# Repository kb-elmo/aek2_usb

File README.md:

# AEK II USB

[![CC BY-NC-SA 4.0][cc-by-nc-sa-shield]][cc-by-nc-sa]

## This project is completed and will not get updated anymore.

#### QMK compatible drop-in replacement PCB for the Apple Extended Keyboard II
The PCB is built entirely with THT parts to keep a somewhat "vintage" look to it and it uses the fullsize 40-pin DIP package ATmega32A.
The controller is placed in the exact same location as the one on the original PCB.

### Partslist
Most of the parts in this list are just examples and they can be replaced with any component with the same specs.  
They don't have to be from any specific manufacturer or brand to work on this board.

The USB breakout PCB/Daughterboard is NOT included in this repo. You will have to find one yourself.  
Pretty much any kind of breakout board that has usable VCC, GND, D+ and D- pins should work for this.  
Example: https://www.adafruit.com/product/1764

|Count|Part|Designator|Octopart URL|
|-|-|-|-|
|1|ATmega32A 40 pin DIP (32L works too)|U1|[Atmega32a-pu](https://octopart.com/atmega32a-pu-microchip-77760288)|
|1|40 pin DIP socket (optional but highly recommended)|U1|[TE Connectivity 1-2199299-5](https://octopart.com/1-2199299-5-te+connectivity-34963610)|
|1|2x3 pin header 2.54mm (for ISP flashing)|AVR1|[Würth 61200621721](https://octopart.com/61200621721-würth+elektronik-32855457)| 
|1|JST PH 2mm 4pin connector + cable|J1, J2|[JST S4B-PH-K-S](https://octopart.com/s4b-ph-k-s+%28lf%29%28sn%29-jst-5373077)|
|1|USB breakout PCB||[Adafruit 1833](https://octopart.com/1833-adafruit+industries-53099556)|
|1|500 mA polyfuse|F1|[Bourns MF-R050](https://octopart.com/mf-r050-bourns-19418)|
|2|6mm momentary push buttons|RESET1, BOOT1|[TE Connectivity 1825910-6](https://octopart.com/1825910-6-te+connectivity-42270338)|
|1|16 MHz quarz crystal|XTAL1|[Raltron AS-16.000-18](https://octopart.com/as-16.000-18-raltron+electronics-973373)|
|1|4.7 uF electrolytic capacitor|C1|[Panasonic ECA-1HM4R7I](https://octopart.com/eca-1hm4r7i-panasonic-39478610)|
|2|100 nF ceramic disk capacitor|C2, C3|[Kemet C315C104M5U5TA](https://octopart.com/c315c104m5u5ta-kemet-83288)|
|2|22 pF ceramic disk capacitor|C4, C5|[Kemet C317C220J1G5TA](https://octopart.com/c317c220j1g5ta-kemet-1747641)|
|1|10 kΩ resistor|R4|[Multicomp MF25 10k](https://octopart.com/mf25+10k-multicomp-2697429)|
|2|68 Ω resistor|R2, R3|[Multicomp MF25 68R](https://octopart.com/mf25+68r-multicomp-5364489)|
|4|1.5 kΩ resistor|R1, R5, R6, R7|[Multicomp MF25 1k5](https://octopart.com/mf25+1k5-multicomp-5372506)|
|3|5mm LED (for the lock indicators)|LED1, LED2, LED3|[Vishay TLHG5400](https://octopart.com/tlhg5400-vishay-39403037)|
|2|3.6 V zener diode (DO-35 BZX55C3V6)|D1, D2|[ON Semiconductor BZX85C3V6](https://octopart.com/bzx85c3v6-on+semiconductor-84409073)|
|105|universal switching diode (DO-35 1N4148)|D3-D107|[ON Semiconductor 1N4148](https://octopart.com/1n4148-on+semiconductor-6807167)|

#### Some pictures of the first finished PCB

---
This work is licensed under a
[Creative Commons Attribution-NonCommercial-ShareAlike 4.0 International License][cc-by-nc-sa].

[![CC BY-NC-SA 4.0][cc-by-nc-sa-image]][cc-by-nc-sa]

[cc-by-nc-sa]: http://creativecommons.org/licenses/by-nc-sa/4.0/
[cc-by-nc-sa-image]: https://licensebuttons.net/l/by-nc-sa/4.0/88x31.png
[cc-by-nc-sa-shield]: https://img.shields.io/badge/License-CC%20BY--NC--SA%204.0-lightgrey.svg

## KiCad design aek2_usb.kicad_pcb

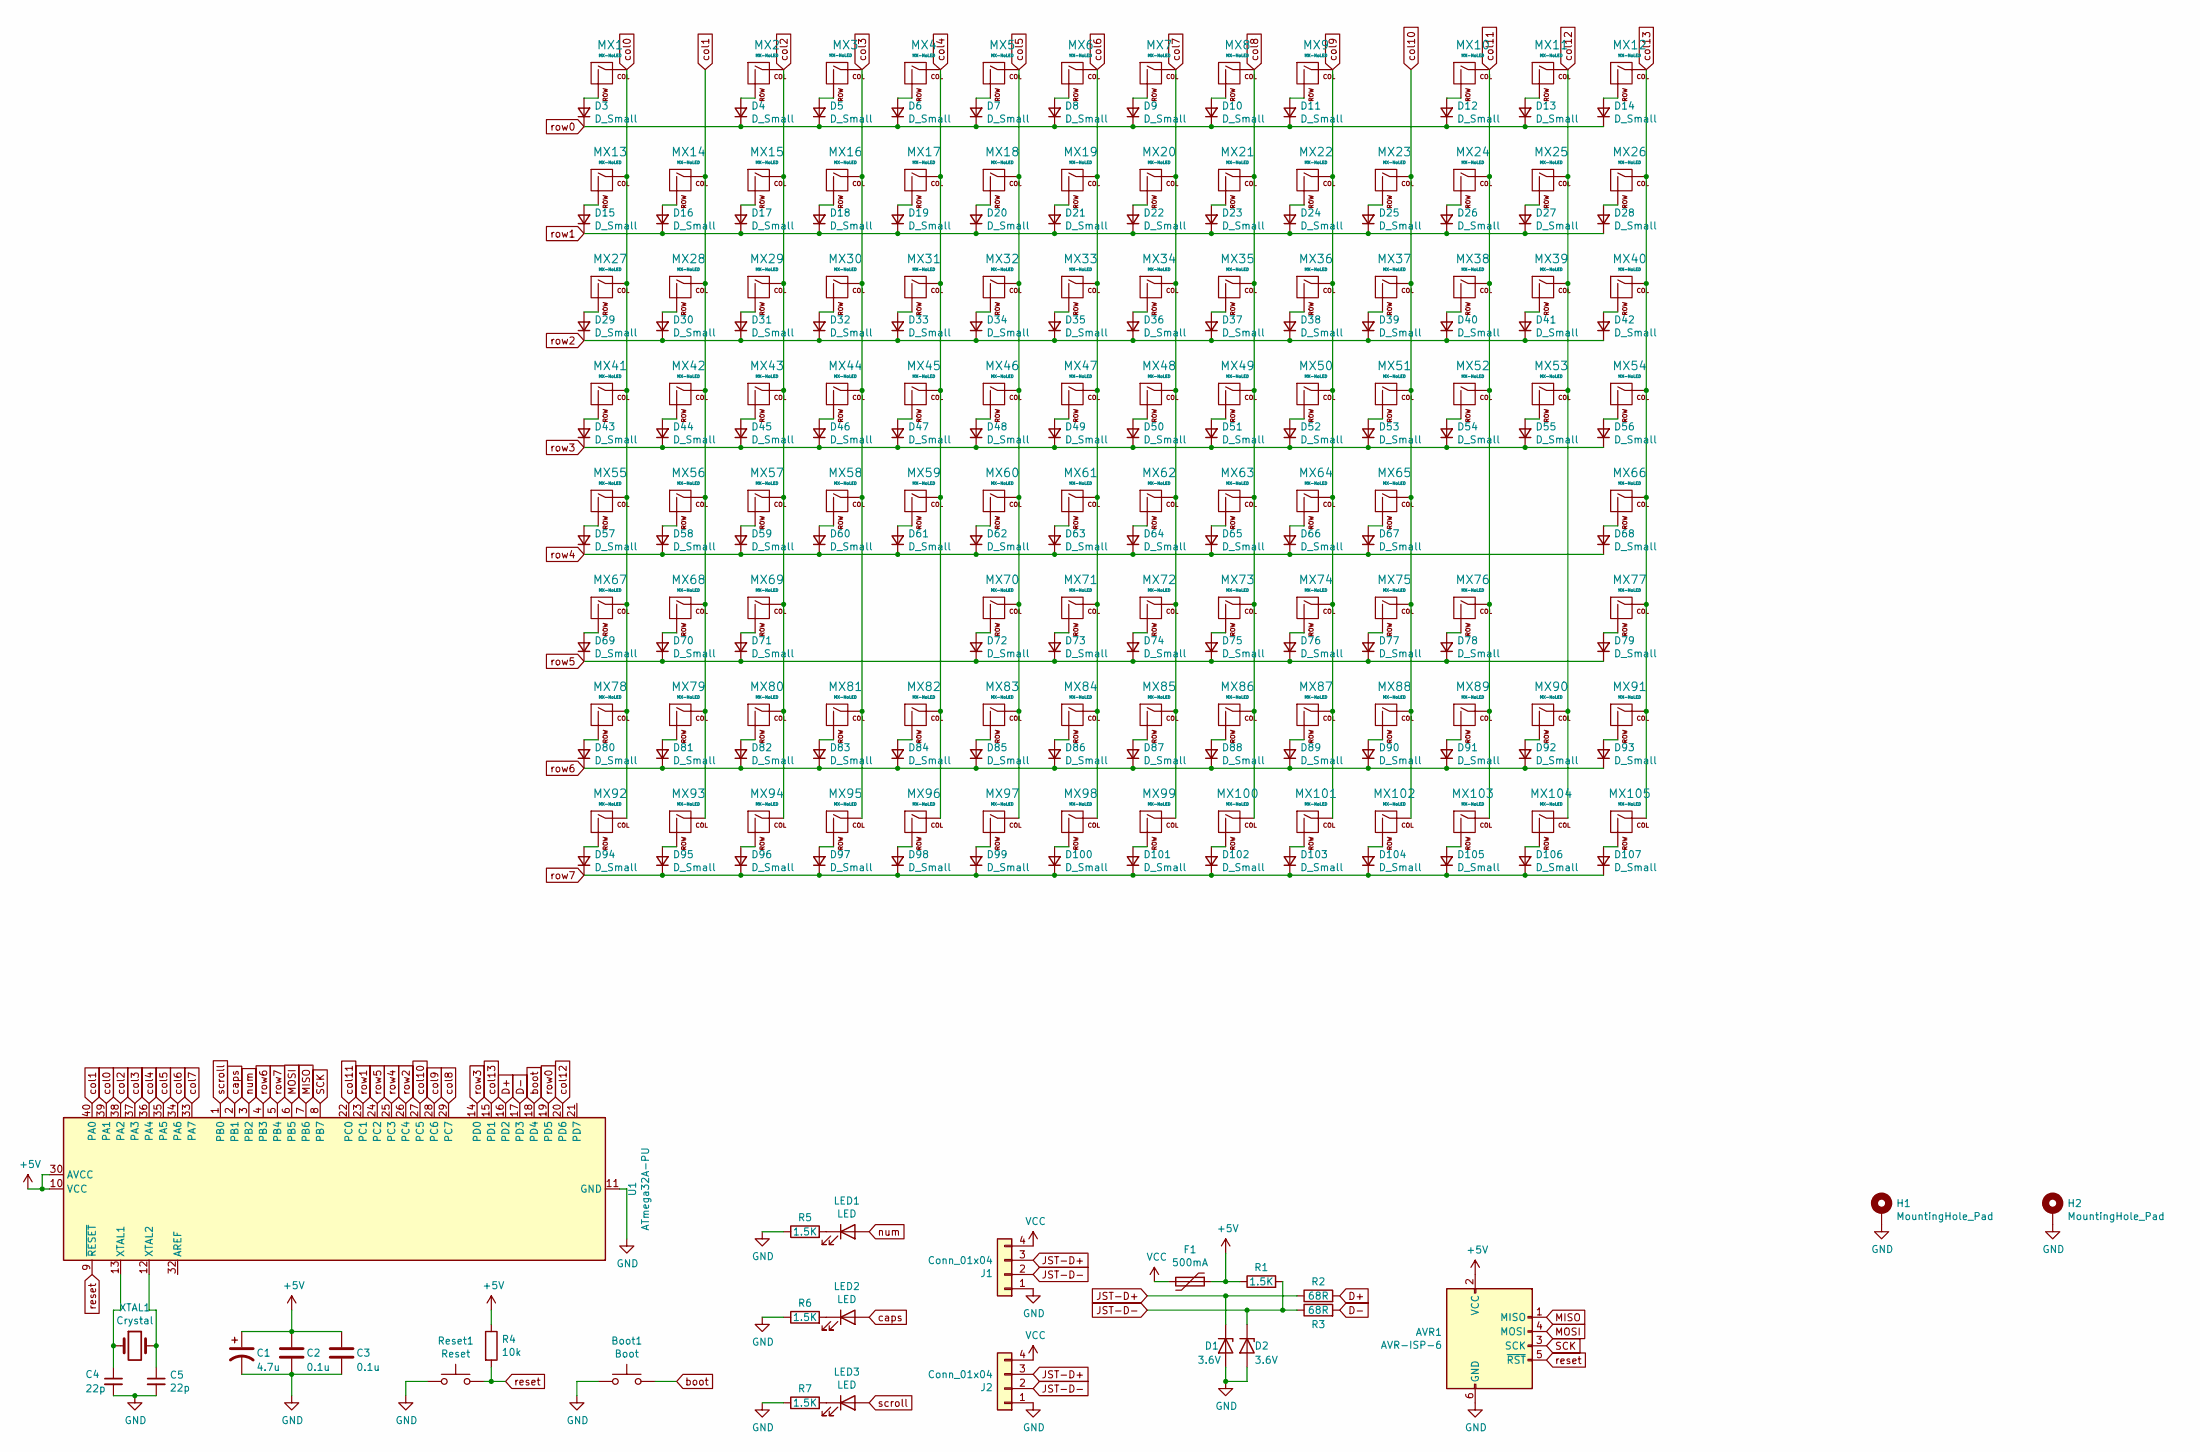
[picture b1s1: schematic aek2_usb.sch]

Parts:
AVR1: AVR-ISP-6; PinHeader_2x03_P2.54mm_Horizontal
Boot1: Boot; SW_PUSH_6mm
C1: 4.7u; CP_Radial_D5.0mm_P2.50mm
C2, C3: 0.1u; C_Disc_D3.0mm_W2.0mm_P2.50mm
C4, C5: 22p; C_Disc_D6.0mm_W2.5mm_P5.00mm
D1, D2: 3.6V; D_DO-35_SOD27_P7.62mm_Horizontal
D3, D4, D5, D6, D7, D8, D9, D10, D11, D12, D13, D14, D15, D16, D17, D18, D19, D20, D21, D22, D23, D24, D25, D26, D27, D28, D29, D30, D31, D32, D33, D34, D35, D36, D37, D38, D39, D40, D41, D42, D43, D44, D45, D46, D47, D48, D49, D50, D51, D52, D53, D54, D55, D56, D57, D58, D59, D60, D61, D62, D63, D64, D65, D66, D67, D68, D69, D70, D71, D72, D73, D74, D75, D76, D77, D78, D79, D80, D81, D82, D83, D84, D85, D86, D87, D88, D89, D90, D91, D92, D93, D94, D95, D96, D97, D98, D99, D100, D101, D102, D103, D104, D105, D106, D107: D_Small; D_DO-35_SOD27_P7.62mm_Horizontal
F1: 500mA; Fuse_Littelfuse_395Series
H1, H2: MountingHole_Pad; screw-hole
J1, J2: Conn_01x04; JST_PH_S4B-PH-K_1x04_P2.00mm_Horizontal
LED1, LED2, LED3: LED; LED_D5.0mm
MX1, MX2, MX3, MX4, MX5, MX6, MX7, MX8, MX9, MX10, MX11, MX12, MX13, MX14, MX15, MX16, MX17, MX18, MX19, MX20, MX21, MX22, MX23, MX24, MX25, MX28, MX29, MX30, MX31, MX32, MX33, MX34, MX35, MX36, MX37, MX38, MX39, MX42, MX43, MX44, MX45, MX46, MX47, MX48, MX49, MX50, MX51, MX52, MX53, MX56, MX57, MX58, MX59, MX60, MX61, MX62, MX63, MX64, MX65, MX70, MX71, MX72, MX73, MX74, MX78, MX79, MX80, MX81, MX82, MX83, MX84, MX85, MX86, MX87, MX88, MX89, MX90, MX91, MX92, MX93, MX94, MX95, MX96, MX97, MX98, MX99, MX101, MX103, MX104, MX105: MX-NoLED; ALPS-1U
MX26, MX100, MX102: MX-NoLED; ALPS-2U
MX27, MX40, MX67, MX69, MX75, MX77: MX-NoLED; ALPS-1.5U
MX41: MX-NoLED; ALPS-1.75U
MX54, MX55: MX-NoLED; ALPS-2.25U
MX66: MX-NoLED; ALPS-2.75U
MX68, MX76: MX-NoLED; ALPS-1.25U
R1, R5, R6, R7: 1.5K; R_Axial_DIN0207_L6.3mm_D2.5mm_P10.16mm_Horizontal
R2, R3: 68R; R_Axial_DIN0207_L6.3mm_D2.5mm_P10.16mm_Horizontal
R4: 10k; R_Axial_DIN0207_L6.3mm_D2.5mm_P10.16mm_Horizontal
Reset1: Reset; SW_PUSH_6mm
U1: ATmega32A-PU; DIP-40_W15.24mm_Socket
XTAL1: Crystal; Crystal_HC49-4H_Vertical

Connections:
+5V: AVR1.2 (VCC), C1.1, C2.1, C3.1, F1.1, R1.1, R4.1, U1.10 (VCC), U1.30 (AVCC)
D+: R2.2, U1.16 (PD2)
D-: R3.2, U1.17 (PD3)
GND: AVR1.6 (GND), Boot1.1, C1.2, C2.2, C3.2, C4.2, C5.2, D1.2 (A), D2.2 (A), H1.1, H2.1, J1.1, J2.1, R5.1, R6.1, R7.1, Reset1.1, U1.11 (GND), U1.31 (GND)
JST-D+: D1.1 (K), J1.3, J2.3, R2.1
JST-D-: D2.1 (K), J1.2, J2.2, R1.2, R3.1
MISO: AVR1.1 (MISO), U1.7 (PB6)
MOSI: AVR1.4 (MOSI), U1.6 (PB5)
unnamed: C4.1, U1.13 (XTAL1), XTAL1.1
unnamed: C5.1, U1.12 (XTAL2), XTAL1.2
unnamed: D3.2 (A), MX1.2 (ROW)
unnamed: D4.2 (A), MX2.2 (ROW)
unnamed: D5.2 (A), MX3.2 (ROW)
unnamed: D6.2 (A), MX4.2 (ROW)
unnamed: D7.2 (A), MX5.2 (ROW)
unnamed: D8.2 (A), MX6.2 (ROW)
unnamed: D9.2 (A), MX7.2 (ROW)
unnamed: D10.2 (A), MX8.2 (ROW)
unnamed: D11.2 (A), MX9.2 (ROW)
unnamed: D12.2 (A), MX10.2 (ROW)
unnamed: D13.2 (A), MX11.2 (ROW)
unnamed: D14.2 (A), MX12.2 (ROW)
unnamed: D15.2 (A), MX13.2 (ROW)
unnamed: D16.2 (A), MX14.2 (ROW)
unnamed: D17.2 (A), MX15.2 (ROW)
unnamed: D18.2 (A), MX16.2 (ROW)
unnamed: D19.2 (A), MX17.2 (ROW)
unnamed: D20.2 (A), MX18.2 (ROW)
unnamed: D21.2 (A), MX19.2 (ROW)
unnamed: D22.2 (A), MX20.2 (ROW)
unnamed: D23.2 (A), MX21.2 (ROW)
unnamed: D24.2 (A), MX22.2 (ROW)
unnamed: D25.2 (A), MX23.2 (ROW)
unnamed: D26.2 (A), MX24.2 (ROW)
unnamed: D27.2 (A), MX25.2 (ROW)
unnamed: D28.2 (A), MX26.2 (ROW)
unnamed: D29.2 (A), MX27.2 (ROW)
unnamed: D30.2 (A), MX28.2 (ROW)
unnamed: D31.2 (A), MX29.2 (ROW)
unnamed: D32.2 (A), MX30.2 (ROW)
unnamed: D33.2 (A), MX31.2 (ROW)
unnamed: D34.2 (A), MX32.2 (ROW)
unnamed: D35.2 (A), MX33.2 (ROW)
unnamed: D36.2 (A), MX34.2 (ROW)
unnamed: D37.2 (A), MX35.2 (ROW)
unnamed: D38.2 (A), MX36.2 (ROW)
unnamed: D39.2 (A), MX37.2 (ROW)
unnamed: D40.2 (A), MX38.2 (ROW)
unnamed: D41.2 (A), MX39.2 (ROW)
unnamed: D42.2 (A), MX40.2 (ROW)
unnamed: D43.2 (A), MX41.2 (ROW)
unnamed: D44.2 (A), MX42.2 (ROW)
unnamed: D45.2 (A), MX43.2 (ROW)
unnamed: D46.2 (A), MX44.2 (ROW)
unnamed: D47.2 (A), MX45.2 (ROW)
unnamed: D48.2 (A), MX46.2 (ROW)
unnamed: D49.2 (A), MX47.2 (ROW)
unnamed: D50.2 (A), MX48.2 (ROW)
unnamed: D51.2 (A), MX49.2 (ROW)
unnamed: D52.2 (A), MX50.2 (ROW)
unnamed: D53.2 (A), MX51.2 (ROW)
unnamed: D54.2 (A), MX52.2 (ROW)
unnamed: D55.2 (A), MX53.2 (ROW)
unnamed: D56.2 (A), MX54.2 (ROW)
unnamed: D57.2 (A), MX55.2 (ROW)
unnamed: D58.2 (A), MX56.2 (ROW)
unnamed: D59.2 (A), MX57.2 (ROW)
unnamed: D60.2 (A), MX58.2 (ROW)
unnamed: D61.2 (A), MX59.2 (ROW)
unnamed: D62.2 (A), MX60.2 (ROW)
unnamed: D63.2 (A), MX61.2 (ROW)
unnamed: D64.2 (A), MX62.2 (ROW)
unnamed: D65.2 (A), MX63.2 (ROW)
unnamed: D66.2 (A), MX64.2 (ROW)
unnamed: D67.2 (A), MX65.2 (ROW)
unnamed: D68.2 (A), MX66.2 (ROW)
unnamed: D69.2 (A), MX67.2 (ROW)
unnamed: D70.2 (A), MX68.2 (ROW)
unnamed: D71.2 (A), MX69.2 (ROW)
unnamed: D72.2 (A), MX70.2 (ROW)
unnamed: D73.2 (A), MX71.2 (ROW)
unnamed: D74.2 (A), MX72.2 (ROW)
unnamed: D75.2 (A), MX73.2 (ROW)
unnamed: D76.2 (A), MX74.2 (ROW)
unnamed: D77.2 (A), MX75.2 (ROW)
unnamed: D78.2 (A), MX76.2 (ROW)
unnamed: D79.2 (A), MX77.2 (ROW)
unnamed: D80.2 (A), MX78.2 (ROW)
unnamed: D81.2 (A), MX79.2 (ROW)
unnamed: D82.2 (A), MX80.2 (ROW)
unnamed: D83.2 (A), MX81.2 (ROW)
unnamed: D84.2 (A), MX82.2 (ROW)
unnamed: D85.2 (A), MX83.2 (ROW)
unnamed: D86.2 (A), MX84.2 (ROW)
unnamed: D87.2 (A), MX85.2 (ROW)
unnamed: D88.2 (A), MX86.2 (ROW)
unnamed: D89.2 (A), MX87.2 (ROW)
unnamed: D90.2 (A), MX88.2 (ROW)
unnamed: D91.2 (A), MX89.2 (ROW)
unnamed: D92.2 (A), MX90.2 (ROW)
unnamed: D93.2 (A), MX91.2 (ROW)
unnamed: D94.2 (A), MX92.2 (ROW)
unnamed: D95.2 (A), MX93.2 (ROW)
unnamed: D96.2 (A), MX94.2 (ROW)
unnamed: D97.2 (A), MX95.2 (ROW)
unnamed: D98.2 (A), MX96.2 (ROW)
unnamed: D99.2 (A), MX97.2 (ROW)
unnamed: D100.2 (A), MX98.2 (ROW)
unnamed: D101.2 (A), MX99.2 (ROW)
unnamed: D102.2 (A), MX100.2 (ROW)
unnamed: D103.2 (A), MX101.2 (ROW)
unnamed: D104.2 (A), MX102.2 (ROW)
unnamed: D105.2 (A), MX103.2 (ROW)
unnamed: D106.2 (A), MX104.2 (ROW)
unnamed: D107.2 (A), MX105.2 (ROW)
unnamed: LED1.1 (K), R5.2
unnamed: LED2.1 (K), R6.2
unnamed: LED3.1 (K), R7.2
SCK: AVR1.3 (SCK), U1.8 (PB7)
VCC: F1.2, J1.4, J2.4
boot: Boot1.2, U1.18 (PD4)
caps: LED2.2 (A), U1.2 (PB1)
col0: MX1.1 (COL), MX13.1 (COL), MX27.1 (COL), MX41.1 (COL), MX55.1 (COL), MX67.1 (COL), MX78.1 (COL), MX92.1 (COL), U1.39 (PA1)
col1: MX14.1 (COL), MX28.1 (COL), MX42.1 (COL), MX56.1 (COL), MX68.1 (COL), MX79.1 (COL), MX93.1 (COL), U1.40 (PA0)
col2: MX2.1 (COL), MX15.1 (COL), MX29.1 (COL), MX43.1 (COL), MX57.1 (COL), MX69.1 (COL), MX80.1 (COL), MX94.1 (COL), U1.38 (PA2)
col3: MX3.1 (COL), MX16.1 (COL), MX30.1 (COL), MX44.1 (COL), MX58.1 (COL), MX81.1 (COL), MX95.1 (COL), U1.37 (PA3)
col4: MX4.1 (COL), MX17.1 (COL), MX31.1 (COL), MX45.1 (COL), MX59.1 (COL), MX82.1 (COL), MX96.1 (COL), U1.36 (PA4)
col5: MX5.1 (COL), MX18.1 (COL), MX32.1 (COL), MX46.1 (COL), MX60.1 (COL), MX70.1 (COL), MX83.1 (COL), MX97.1 (COL), U1.35 (PA5)
col6: MX6.1 (COL), MX19.1 (COL), MX33.1 (COL), MX47.1 (COL), MX61.1 (COL), MX71.1 (COL), MX84.1 (COL), MX98.1 (COL), U1.34 (PA6)
col7: MX7.1 (COL), MX20.1 (COL), MX34.1 (COL), MX48.1 (COL), MX62.1 (COL), MX72.1 (COL), MX85.1 (COL), MX99.1 (COL), U1.33 (PA7)
col8: MX8.1 (COL), MX21.1 (COL), MX35.1 (COL), MX49.1 (COL), MX63.1 (COL), MX73.1 (COL), MX86.1 (COL), MX100.1 (COL), U1.29 (PC7)
col9: MX9.1 (COL), MX22.1 (COL), MX36.1 (COL), MX50.1 (COL), MX64.1 (COL), MX74.1 (COL), MX87.1 (COL), MX101.1 (COL), U1.28 (PC6)
col10: MX23.1 (COL), MX37.1 (COL), MX51.1 (COL), MX65.1 (COL), MX75.1 (COL), MX88.1 (COL), MX102.1 (COL), U1.27 (PC5)
col11: MX10.1 (COL), MX24.1 (COL), MX38.1 (COL), MX52.1 (COL), MX76.1 (COL), MX89.1 (COL), MX103.1 (COL), U1.22 (PC0)
col12: MX11.1 (COL), MX25.1 (COL), MX39.1 (COL), MX53.1 (COL), MX90.1 (COL), MX104.1 (COL), U1.20 (PD6)
col13: MX12.1 (COL), MX26.1 (COL), MX40.1 (COL), MX54.1 (COL), MX66.1 (COL), MX77.1 (COL), MX91.1 (COL), MX105.1 (COL), U1.15 (PD1)
num: LED1.2 (A), U1.3 (PB2)
reset: AVR1.5 (~RST), R4.2, Reset1.2, U1.9 (~RESET)
row0: D3.1 (K), D4.1 (K), D5.1 (K), D6.1 (K), D7.1 (K), D8.1 (K), D9.1 (K), D10.1 (K), D11.1 (K), D12.1 (K), D13.1 (K), D14.1 (K), U1.19 (PD5)
row1: D15.1 (K), D16.1 (K), D17.1 (K), D18.1 (K), D19.1 (K), D20.1 (K), D21.1 (K), D22.1 (K), D23.1 (K), D24.1 (K), D25.1 (K), D26.1 (K), D27.1 (K), D28.1 (K), U1.23 (PC1)
row2: D29.1 (K), D30.1 (K), D31.1 (K), D32.1 (K), D33.1 (K), D34.1 (K), D35.1 (K), D36.1 (K), D37.1 (K), D38.1 (K), D39.1 (K), D40.1 (K), D41.1 (K), D42.1 (K), U1.26 (PC4)
row3: D43.1 (K), D44.1 (K), D45.1 (K), D46.1 (K), D47.1 (K), D48.1 (K), D49.1 (K), D50.1 (K), D51.1 (K), D52.1 (K), D53.1 (K), D54.1 (K), D55.1 (K), D56.1 (K), U1.14 (PD0)
row4: D57.1 (K), D58.1 (K), D59.1 (K), D60.1 (K), D61.1 (K), D62.1 (K), D63.1 (K), D64.1 (K), D65.1 (K), D66.1 (K), D67.1 (K), D68.1 (K), U1.25 (PC3)
row5: D69.1 (K), D70.1 (K), D71.1 (K), D72.1 (K), D73.1 (K), D74.1 (K), D75.1 (K), D76.1 (K), D77.1 (K), D78.1 (K), D79.1 (K), U1.24 (PC2)
row6: D80.1 (K), D81.1 (K), D82.1 (K), D83.1 (K), D84.1 (K), D85.1 (K), D86.1 (K), D87.1 (K), D88.1 (K), D89.1 (K), D90.1 (K), D91.1 (K), D92.1 (K), D93.1 (K), U1.4 (PB3)
row7: D94.1 (K), D95.1 (K), D96.1 (K), D97.1 (K), D98.1 (K), D99.1 (K), D100.1 (K), D101.1 (K), D102.1 (K), D103.1 (K), D104.1 (K), D105.1 (K), D106.1 (K), D107.1 (K), U1.5 (PB4)
scroll: LED3.2 (A), U1.1 (PB0)

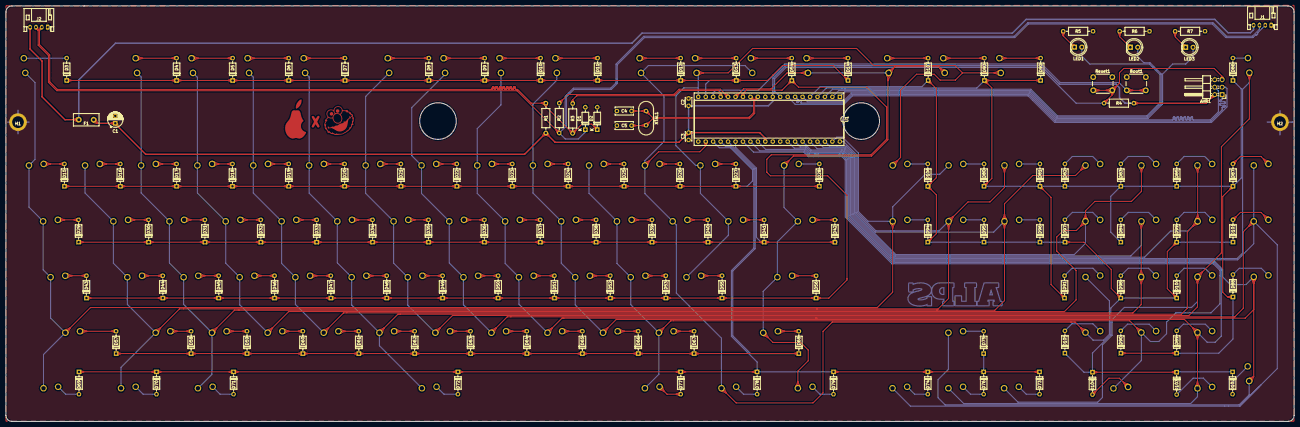
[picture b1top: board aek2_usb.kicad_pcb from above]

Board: 2 copper layers, 439.0 x 141.6 mm, 237 parts (0 on the bottom side), 147 nets.

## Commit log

2020-07-19 change logo
2020-07-19 remove unnecessary files
2020-07-19 cleanup
2020-07-20 change license
2020-07-29 added firmware
2020-07-30 added ISO support (UNTESTED!)
2020-07-30 fix ISO enter position (still untested!)
2020-07-30 add teardrops
2020-07-30 remove ISO support because layout is wrong
2020-07-30 fix teardrops
2021-01-15 add VIA keymap
